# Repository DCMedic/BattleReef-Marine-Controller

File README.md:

# BattleReef Marine Controller

BattleReef Marine Controller is a secure, event-driven cyber-physical platform for marine aquarium monitoring, automation, and device control. The current stack combines a FastAPI/SQLAlchemy backend, TimescaleDB/PostgreSQL telemetry storage, mutually authenticated MQTT transport, an authenticated HTTP control plane, and a React/Vite operator interface.

## Control flow

The normal remote-control lifecycle is intentionally single-path:

1. An authenticated node publishes telemetry over MQTT/TLS.
2. Mosquitto authorizes the certificate identity against the topic ACL.
3. The backend verifies topic/payload identity, evaluates telemetry plausibility, and persists the reading.
4. Implausible readings are retained for forensics as `quality=suspect` but are excluded from trusted automation.
5. Rules, schedules, and the safety watchdog may create a queued command using only recent trusted telemetry where sensor evidence is involved.
6. The command dispatcher publishes the queued command to the target device and marks it `dispatched`.
7. The authenticated device executes the command and publishes an ACK containing its correlation ID and resulting state.
8. The backend verifies device identity, command correlation, and reported state before marking the command completed.
9. Independent physical evidence can then challenge the device's self-reported state.

Publishing a command is not treated as successful actuation. An ACK proves what a device reports; independent physical verification provides a separate evidence layer for what the system appears to be doing physically.

## HTTP authentication and RBAC

The operator API uses Argon2 password hashing and short-lived HS256 bearer tokens. Tokens are bound to username, role, principal type, issuer/audience, and a database token version. Password, role, or activation changes invalidate previously issued sessions. Browser tokens are stored only in `sessionStorage`.

Repeated bad credentials trigger a temporary database-backed lockout. The role hierarchy is `viewer`, `operator`, `engineer`, and `administrator`, with both human `user` and non-interactive `service` principals supported.

## MQTT identity and authorization

MQTT listens on TLS port `8883` and requires an X.509 client certificate. Mosquitto uses certificate CN as MQTT identity, anonymous access is disabled, and broker ACLs restrict nodes/devices to their own telemetry, ACK, and command namespaces.

## Audit trail

Security, command, operator, device-health, telemetry-quarantine, and independent physical-verification transitions are persisted in PostgreSQL as an append-only SHA-256 hash-chained journal. Historical audit events have read/integrity APIs but no update/delete API.

## Telemetry plausibility and quarantine

Before a new reading is trusted, BattleReef evaluates conservative physical bounds and selected rate-of-change/correlation rules. Current examples include temperature, pH, salinity, sump level, dissolved oxygen, ORP, flow, RPM, and dedicated power channels. Large salinity changes are additionally checked against recent sump-level movement from the same authenticated telemetry source.

A failed plausibility check does not delete data. The reading is persisted as `quality=suspect`, a runtime alert is raised, and a durable audit event records the quarantine reason. Automation reads use only `quality=good` telemetry. Temperature automation also rejects trusted readings older than 120 seconds, preventing fallback to stale-but-valid data after a sensor begins producing implausible samples.

The safety watchdog follows the same trust model. Critical temperature/sump actions and threshold evaluation require recent trusted data. Leak probes remain deliberately fail-safe: only a trusted `0.0` reading is accepted as dry.

## Independent physical-state verification

A background verifier runs every 15 seconds and compares fresh device-reported state against fresh independent telemetry.

Return-pump verification can use three separate physical domains: `power_return_pump_main` for electrical consumption, `flow_return_main` for hydraulic delivery, and optional `rpm_return_pump_main` for rotational evidence. A contradiction in any available channel is treated as a critical failure. When only one independent signal is installed and agrees, the verifier reports degraded rather than falsely claiming strong multi-signal verification.

Heater relay state is checked against `power_heater_main`, a dedicated isolated heater-circuit power measurement. Aggregate `power_monitor_main` is intentionally not used for this critical assertion because unrelated loads could create false positives.

Critical sensor values can also be challenged by redundant channels. `tank_temp_verify` is compared with `tank_temp_main`, and `sump_level_verify` is compared with `sump_level_main`. Moderate disagreement produces a degraded warning; disagreement beyond twice the configured tolerance becomes critical.

Independent evidence older than 120 seconds is not used to verify state; the result becomes `unknown`. Critical contradictions raise runtime alerts, create tamper-evident audit events, and impose a large device-health penalty. Degraded verification warnings receive a smaller health penalty. Recovery is audited.

Engineers can manually invoke the verifier at `POST /api/v1/physical-verification/evaluate` in addition to the periodic background evaluation.

## Independent verification hardware package

The hardware contract is versioned under `hardware/`:

- `hardware/verification-package-v1.json` is the machine-readable sensor/evidence manifest and threshold contract.
- `hardware/README.md` describes architecture, isolation requirements, evidence topology, MQTT behavior, and maintenance expectations.
- `hardware/commissioning-checklist-v1.md` is the acceptance checklist for bringing real verification hardware into service.

Version 1 defines dedicated heater and return-pump power channels, return flow, optional pump RPM, a redundant tank-temperature probe, and a redundant sump-level channel. Backend tests verify that every sensor named in the hardware manifest exists in the sensor catalog and that manifest thresholds match runtime verification constants.

Any interface connected to AC mains must be galvanically isolated, enclosed, appropriately listed/certified, and installed according to applicable electrical code and manufacturer instructions. BattleReef GPIO/ADC pins, exposed development boards, breadboards, and water-contact sensors must never be connected directly to mains potential.

## Device health monitoring

BattleReef evaluates device/node health every 30 seconds and persists the latest score in `device_health`. Health uses telemetry/state freshness, telemetry quality, command failures/timeouts, ACK state mismatches, average ACK latency, and active independent physical-verification failures.

Health states are `healthy`, `degraded`, `critical`, and `unknown`. Degraded/critical states create runtime alerts; transitions are written to the audit journal. Authenticated viewers can read `/api/v1/device-health`, while engineers can manually request evaluation at `/api/v1/device-health/evaluate`.

## Development fault injection

`tools/simulator/device_fault_injector.py` exercises the real mTLS command/ACK path with `normal`, `drop_ack`, `delayed_ack`, `wrong_state`, and `explicit_failure` behaviors.

`tools/simulator/physical_fault_injector.py` exercises telemetry plausibility and physical verification using development-only mTLS credentials. Scenarios include salinity spikes, zero/present return flow, return-pump power and RPM contradictions, heater power contradictions, and redundant temperature/sump disagreement.

Examples:

```bash
python tools/simulator/physical_fault_injector.py salinity_spike
python tools/simulator/physical_fault_injector.py return_pump_power_zero
python tools/simulator/physical_fault_injector.py verify_temp_disagreement
python tools/simulator/physical_fault_injector.py heater_power_present
```

The fault injectors are external development tools. No production HTTP endpoint can enable them. Never deploy the aggregate development simulator certificates to production hardware.

## Telemetry contract

Telemetry values are numeric throughout the API/database (`value_double`) and timestamps are normalized to UTC. Leak probes use `0.0 = dry` and `1.0 = wet`. Unknown, suspect, or non-dry leak evidence is treated fail-safe.

Dedicated verification channels must represent independently measured physical evidence rather than copied command values or actuator self-reports.

## Local development

```bash
cp .env.example .env
bash ops/mosquitto/generate-dev-pki.sh
docker compose up --build
```

For backend tests:

```bash
cd backend
python -m venv .venv
# Activate .venv for your platform
python -m pip install --upgrade pip
pip install -e ".[dev]"
MQTT_TLS_ENABLED=false pytest
```

For the frontend:

```bash
cd frontend
cp .env.example .env
npm ci
npm run dev
```

## Production certificate provisioning

Production deployments should use a dedicated BattleReef device CA or enterprise PKI. Each hardware node should receive its own private key/certificate and independently revocable identity.

## Database bootstrap

`ops/postgres/init.sql` owns TimescaleDB-specific telemetry initialization. The backend also runs an idempotent SQLAlchemy schema bootstrap at startup so application schema evolution can occur without destructive database-volume resets.

## Continuous integration

GitHub Actions validates pull requests to `main` with repository hygiene, backend regression tests, frontend build/security audit, Compose validation, and a live MQTT mTLS security integration gate. Plausibility boundaries, fail-safe leak semantics, independent physical verification, and the hardware-manifest/runtime contract are regression tested.

## Safety principles

BattleReef treats automation as a cyber-physical safety system. Safety-critical commands use explicit delivery policies, automation commands are deduplicated, safety/schedule/health/physical-verification loops recover from transient errors, remote commands require authenticated ACKs, independent evidence can contradict device self-reports, implausible telemetry is quarantined rather than trusted, and privileged HTTP actions require an authenticated principal with the appropriate role.

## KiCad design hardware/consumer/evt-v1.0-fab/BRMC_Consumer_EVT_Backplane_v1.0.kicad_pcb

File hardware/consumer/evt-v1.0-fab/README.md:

# BRMC Consumer EVT v1.0 modular backplane

This directory is the controlled engineer-review release for the 220 × 78 mm,
six-layer BRMC Consumer modular prototype backplane. The design is generated
deterministically; review the generated KiCad source and the exact successful
CI manufacturing artifact together.

## Controlled scope

The PCB is a passive module-interconnect backplane. It is not the complete
integrated main logic/power board or rear precision-analog board described by
the older v0.9 architecture. The EVT compute endpoint is an official Raspberry
Pi CM5 IO Board revision 2, independently powered at J11 by an official 27 W
USB-C supply. `J_CM5` is a signal-only 16-circuit interface; CM5 power is not
carried on the backplane.

The current generator implements production geometry for all 13 board
connectors:

- Molex C-Grid III 90130-1216 at `J_CM5` and 90130-1224 at `J_MCU`;
- Molex KK 254 22-23-20x1 headers for sensor, field-bus, safety and service
  interfaces; and
- Molex Micro-Fit 3.0 43045-0600/-0400/-0800 right-angle headers, including
  the manufacturer-pattern locator holes, for `J_PWR`, `J_AO` and `J_PWRMOD`.

`connector-production-verification.csv` freezes the design selection and cites
the governing manufacturer evidence. Independent drawing comparison,
first-article keying/orientation, crimp inspection and mating-access acceptance
remain required approval evidence; the file does not claim those events have
already occurred.

## Electrical definition

The source generator, pinout, interconnect schematic, machine-readable netlist,
power budget and harness schedule together define the board-only electrical
interface. A component-level KiCad schematic/ERC result is not asserted because
this artifact contains no active circuitry. The CI validator instead reconciles
the generated endpoint schedule to the PCB and its IPC-D-356 export.

Power routing uses 1.50 mm `24V_IN` and 2.00 mm `5V_SYS` B.Cu trunks. Connector
fan-out is segregated by copper layer, with L2 and L5 reserved as continuous GND
reference planes. GND connector pads connect directly to those planes. The
review package records calculated interface ceilings, conductor gauges,
maximum harness lengths, warm voltage drop and branch-protection requirements.
Unimplemented PSM-01 and daughtercard circuits must be independently reviewed
as separate design objects and must comply with the controlled ceilings.

## Automated gates

The GitHub workflow regenerates all controlled source and review artifacts,
rejects drift, fills the L2/L5 planes in an archived manufacturing copy, runs
KiCad 9 DRC, exports Gerber/drill/position/IPC-D-356/STEP outputs, reconciles
the netlist, validates the complete package, and checksums every artifact. Only
an artifact from a successful run for the exact reviewed commit is acceptable.

## Review package

Start with `BRMC_Consumer_v1.0_Engineer_Review_Index.md` and
`BRMC_Consumer_v1.0_Electrical_Engineering_Review_Package.pdf`. The
interconnect PDF, CSV schedules, KiCad files, enclosure-base candidate and
external return forms are all included in the CI artifact.

## Release status

`release-status.json` and `release-gate-evidence.json` are authoritative. This
revision is **complete for independent engineering review of the passive
backplane scope**, but it is **not a prototype fabrication release**. The
following approvals/evidence cannot be self-issued and remain external gates:

- responsible mechanical engineer approval of the CNC 6061 base and a
  tolerance-aware populated/harness/thermal/service fit record;
- fabricator-returned stackup and DFM approval tied to the exact CI artifact;
- independent qualified electrical/layout review with all findings closed;
- connector/harness first-article orientation, crimp, continuity and access
  evidence; and
- measured EVT startup, steady-state, transient/fault and thermal evidence.

Commercial production, mains connection, and approval of absent module designs
remain prohibited.

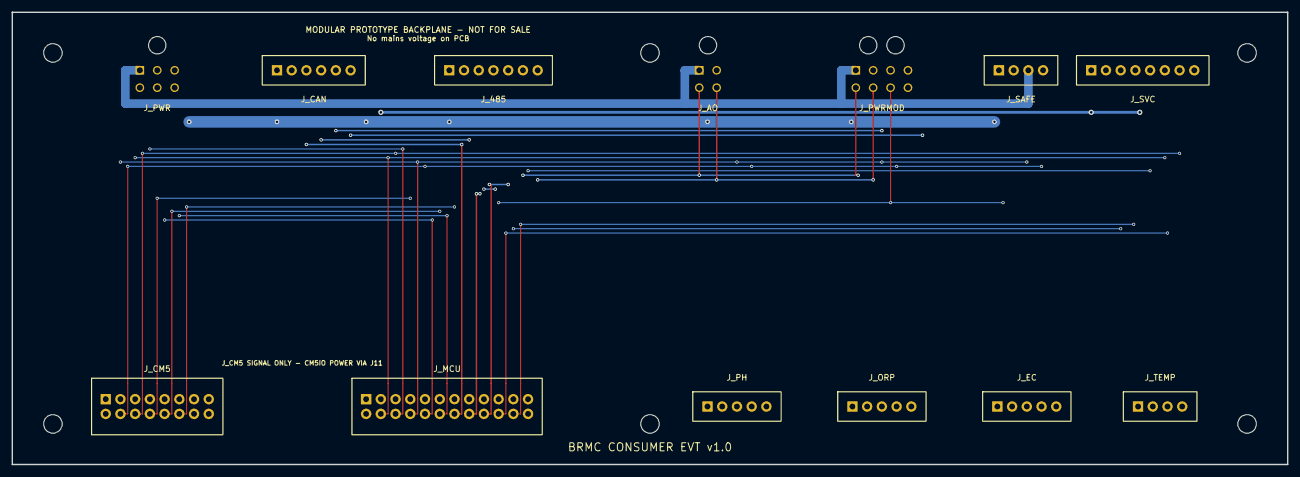
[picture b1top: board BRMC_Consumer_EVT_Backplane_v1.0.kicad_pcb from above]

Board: 6 copper layers, 220.0 x 78.0 mm, 19 parts (0 on the bottom side), 28 nets.

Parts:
H1: MountingHole_3.2mm_M3; MOUNT_M3_H1
H2: MountingHole_3.2mm_M3; MOUNT_M3_H2
H3: MountingHole_3.2mm_M3; MOUNT_M3_H3
H4: MountingHole_3.2mm_M3; MOUNT_M3_H4
H5: MountingHole_3.2mm_M3; MOUNT_M3_H5
H6: MountingHole_3.2mm_M3; MOUNT_M3_H6
J_485: MOLEX_22-23-2071_ISO_RS485_MODULE; HDR_J_485
J_AO: MOLEX_43045-0400_MODBUS_0_10V_8CH; HDR_J_AO
J_CAN: MOLEX_22-23-2061_ISO_CAN_FD_MODULE; HDR_J_CAN
J_CM5: MOLEX_90130-1216_CM5IO_SIGNAL; HDR_J_CM5
J_EC: MOLEX_22-23-2051_ATLAS_EZO_EC_ISO; HDR_J_EC
J_MCU: MOLEX_90130-1224_STM32G0B1_CORE; HDR_J_MCU
J_ORP: MOLEX_22-23-2051_ATLAS_EZO_ORP_ISO; HDR_J_ORP
J_PH: MOLEX_22-23-2051_ATLAS_EZO_PH_ISO; HDR_J_PH
J_PWR: MOLEX_43045-0600_POWER_HARNESS; HDR_J_PWR
J_PWRMOD: MOLEX_43045-0800_POWER_MODULE_BUS; HDR_J_PWRMOD
J_SAFE: MOLEX_22-23-2041_SAFETY_RELAY_DRIVE; HDR_J_SAFE
J_SVC: MOLEX_22-23-2081_SERVICE_DEBUG; HDR_J_SVC
J_TEMP: MOLEX_22-23-2041_DIGITAL_TEMP; HDR_J_TEMP

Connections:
3V3_SYS: J_MCU.3 (3V3_SYS), J_SVC.1 (3V3_SYS), J_TEMP.1 (3V3_SYS)
5V_SYS: J_485.1 (5V_SYS), J_CAN.1 (5V_SYS), J_EC.1 (5V_SYS), J_MCU.1 (5V_SYS), J_ORP.1 (5V_SYS), J_PH.1 (5V_SYS), J_PWR.3 (5V_SYS)
24V_IN: J_AO.1 (24V_IN), J_PWR.1 (24V_IN), J_PWRMOD.1 (24V_IN), J_SAFE.3 (24V_IN)
CAN_H: J_CAN.5 (CAN_H), J_PWRMOD.3 (CAN_H)
CAN_L: J_CAN.6 (CAN_L), J_PWRMOD.4 (CAN_L)
CAN_RX: J_CAN.4 (CAN_RX), J_MCU.15 (CAN_RX)
CAN_TX: J_CAN.3 (CAN_TX), J_MCU.14 (CAN_TX)
CM5_HEARTBEAT: J_CM5.7 (CM5_HEARTBEAT), J_MCU.6 (CM5_HEARTBEAT)
CM5_RX: J_CM5.6 (CM5_RX), J_MCU.5 (CM5_RX), J_SVC.7 (CM5_RX)
CM5_TX: J_CM5.5 (CM5_TX), J_MCU.4 (CM5_TX), J_SVC.6 (CM5_TX)
GND: J_485.2 (GND), J_AO.2 (GND), J_CAN.2 (GND), J_CM5.1 (GND), J_CM5.2 (GND), J_CM5.15 (GND), J_CM5.16 (GND), J_EC.2 (GND), J_MCU.2 (GND), J_MCU.24 (GND), J_ORP.2 (GND), J_PH.2 (GND), J_PWR.2 (GND), J_PWR.4 (GND), J_PWR.6 (GND), J_PWRMOD.2 (GND), J_PWRMOD.8 (GND), J_SAFE.2 (GND), J_SAFE.4 (GND), J_SVC.2 (GND), J_SVC.8 (GND), J_TEMP.2 (GND)
I2C_SCL: J_CM5.3 (I2C_SCL), J_EC.3 (I2C_SCL), J_MCU.8 (I2C_SCL), J_ORP.3 (I2C_SCL), J_PH.3 (I2C_SCL)
I2C_SDA: J_CM5.4 (I2C_SDA), J_EC.4 (I2C_SDA), J_MCU.9 (I2C_SDA), J_ORP.4 (I2C_SDA), J_PH.4 (I2C_SDA)
NRST: J_MCU.23 (NRST), J_SVC.5 (NRST)
RS485_A: J_485.6 (RS485_A), J_AO.3 (RS485_A), J_PWRMOD.5 (RS485_A)
RS485_B: J_485.7 (RS485_B), J_AO.4 (RS485_B), J_PWRMOD.6 (RS485_B)
RS485_DE: J_485.5 (RS485_DE), J_MCU.18 (RS485_DE)
RS485_RX: J_485.4 (RS485_RX), J_MCU.17 (RS485_RX)
RS485_TX: J_485.3 (RS485_TX), J_MCU.16 (RS485_TX)
SAFETY_ACK: J_CM5.8 (SAFETY_ACK), J_MCU.7 (SAFETY_ACK)
SAFETY_ENABLE: J_MCU.19 (SAFETY_ENABLE), J_PWRMOD.7 (SAFETY_ENABLE), J_SAFE.1 (SAFETY_ENABLE)
SPI_CS0: J_CM5.12 (SPI_CS0), J_MCU.13 (SPI_CS0)
SPI_MISO: J_CM5.10 (SPI_MISO), J_MCU.11 (SPI_MISO)
SPI_MOSI: J_CM5.11 (SPI_MOSI), J_MCU.12 (SPI_MOSI)
SPI_SCK: J_CM5.9 (SPI_SCK), J_MCU.10 (SPI_SCK)
SWCLK: J_MCU.22 (SWCLK), J_SVC.4 (SWCLK)
SWDIO: J_MCU.21 (SWDIO), J_SVC.3 (SWDIO)
TEMP_DATA: J_MCU.20 (TEMP_DATA), J_TEMP.3 (TEMP_DATA)

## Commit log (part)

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2026-03-09 new file: .env.example new file: backend/alembic.ini new file: backend/app/api/deps.py new file: backend/app/api/routes/alerts.py new file: backend/app/api/routes/commands.py new file: backend/app/ap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
2026-03-09 new file: .env modified: .env.example new file: backend/app/__pycache__/config.cpython-312.pyc new file: backend/app/__pycache__/main.cpython-312.pyc new file: backend/app/api/routes/__pycache__/heal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
2026-03-10 modified: backend/app/__pycache__/main.cpython-312.pyc modified: backend/app/api/routes/__pycache__/telemetry.cpython-312.pyc modified: backend/app/api/routes/telemetry.py new file: backend/app/db/__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
2026-03-10 modified: backend/app/__pycache__/config.cpython-312.pyc modified: backend/app/__pycache__/main.cpython-312.pyc modified: backend/app/config.py modified: backend/app/main.py new file: backend/app/ser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
2026-03-10 new file: backend/app/mqtt/__pycache__/topics.cpython-312.pyc modified: backend/app/mqtt/topics.py modified: backend/app/services/__pycache__/mqtt_listener.cpython-312.pyc modified: backend/app/servi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
2026-03-10 modified: backend/app/__pycache__/config.cpython-312.pyc modified: backend/app/__pycache__/main.cpython-312.pyc new file: backend/app/api/routes/__pycache__/commands.cpython-312.pyc modified: backend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
2026-03-10 modified: backend/app/services/__pycache__/mqtt_listener.cpython-312.pyc modified: backend/app/services/mqtt_listener.py
2026-03-10 modified: backend/app/__pycache__/main.cpython-312.pyc new file: backend/app/api/routes/__pycache__/device_states.cpython-312.pyc new file: backend/app/api/routes/device_states.py new file: backend/a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
2026-03-10 modified: backend/app/__pycache__/main.cpython-312.pyc modified: backend/app/api/routes/__pycache__/commands.cpython-312.pyc modified: backend/app/main.py modified: backend/app/mqtt/__pycache__/topic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
2026-03-10 modified: backend/app/__pycache__/main.cpython-312.pyc modified: backend/app/mqtt/__pycache__/topics.cpython-312.pyc modified: backend/app/mqtt/topics.py modified: backend/app/services/__pycache__/co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
2026-03-10 modified: backend/app/__pycache__/main.cpython-312.pyc new file: backend/app/api/routes/__pycache__/system.cpython-312.pyc new file: backend/app/api/routes/system.py modified: backend/app/db/models/_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
2026-03-10 modified: frontend/src/api/client.ts modified: frontend/src/api/queries.ts modified: frontend/src/components/DeviceStateTile.tsx modified: frontend/src/components/MetricCard.tsx new file: frontend/sr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
2026-03-10 modified: .env new file: frontend/.env new file: frontend/index.html new file: frontend/node_modules/.bin/baseline-browser-mapping new file: frontend/node_modules/.bin/baseline-browser-mapping.cmd ne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
2026-03-10 Frontend Telemetry Charts
2026-03-11 modified: frontend/src/api/client.ts modified: frontend/src/api/queries.ts new file: frontend/src/components/ManualControlPanel.tsx new file: frontend/src/components/RecentCommandsTable.tsx new file: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
2026-03-11 modified: backend/app/api/routes/__pycache__/device_states.cpython-312.pyc modified: backend/app/api/routes/device_states.py modified: backend/app/services/__pycache__/device_state_service.cpython-31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
2026-03-11 modified: backend/app/services/__pycache__/command_service.cpython-312.pyc modified: backend/app/services/command_service.py modified: frontend/src/components/ManualControlPanel.tsx
2026-03-11 modified: backend/app/api/routes/__pycache__/commands.cpython-312.pyc modified: backend/app/api/routes/commands.py modified: backend/app/services/__pycache__/rule_engine.cpython-312.pyc modified: bac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
2026-03-11 modified: backend/app/__pycache__/main.cpython-312.pyc new file: backend/app/api/routes/__pycache__/schedules.cpython-312.pyc new file: backend/app/api/routes/schedules.py modified: backend/app/db/__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
2026-03-11 modified: frontend/src/api/queries.ts new file: frontend/src/components/ScheduleManagerPanel.tsx modified: frontend/src/pages/Dashboard.tsx modified: frontend/src/types/index.ts
2026-03-11 modified: frontend/src/components/ScheduleManagerPanel.tsx
2026-03-11 modified: frontend/src/api/client.ts modified: frontend/src/api/queries.ts
2026-03-11 new file: frontend/src/components/WeeklyScheduleTimeline.tsx modified: frontend/src/pages/Dashboard.tsx
2026-03-11 Created separate logical pages to fit cards into.
2026-03-11 modified: frontend/src/App.tsx
2026-03-11 modified: frontend/src/App.tsx modified: frontend/src/pages/OperationsPage.tsx
2026-03-16 new file: backend/control/heater_controller.py new file: backend/devices/base_device.py new file: backend/devices/feeder_device.py new file: backend/devices/heater_device.py new file: backend/devices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
2026-03-16 new file: backend/api/devices.py modified: backend/app/api/routes/devices.py modified: backend/app/main.py new file: backend/bootstrap_devices.py modified: backend/control/heater_controller.py modifi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
2026-03-16 modified: backend/app/__pycache__/main.cpython-312.pyc new file: backend/app/api/routes/__pycache__/alerts.cpython-312.pyc new file: backend/app/api/routes/__pycache__/devices.cpython-312.pyc
2026-03-16 modified: backend/app/__pycache__/main.cpython-312.pyc modified: backend/app/api/routes/__pycache__/devices.cpython-312.pyc
2026-03-17 deleted: backend/api/devices.py new file: backend/app/__init__.py new file: backend/app/__pycache__/__init__.cpython-312.pyc new file: backend/app/__pycache__/bootstrap_devices.cpython-312.pyc modifi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
2026-03-17 modified: backend/app/api/routes/__pycache__/commands.cpython-312.pyc modified: backend/app/api/routes/__pycache__/device_states.cpython-312.pyc modified: backend/app/api/routes/__pycache__/health.cp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
2026-03-17 modified: backend/app/__pycache__/main.cpython-312.pyc modified: backend/app/api/routes/__pycache__/alerts.cpython-312.pyc modified: backend/app/api/routes/__pycache__/commands.cpython-312.pyc modifi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
2026-03-17 modified: backend/app/api/routes/commands.py modified: backend/app/main.py modified: backend/app/services/command_dispatcher.py modified: backend/app/services/command_service.py new file: backend/app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
2026-03-18 modified: backend/app/api/routes/alerts.py modified: backend/app/api/routes/health.py new file: backend/app/core/runtime_alerts.py modified: backend/app/main.py new file: backend/app/services/safety_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
2026-03-18 modified: backend/app/__pycache__/main.cpython-312.pyc modified: backend/app/api/routes/__pycache__/alerts.cpython-312.pyc modified: backend/app/api/routes/__pycache__/commands.cpython-312.pyc modifi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
2026-03-18 modified: backend/app/core/__pycache__/api_self_test.cpython-312.pyc modified: backend/app/core/api_self_test.py modified: backend/app/services/__pycache__/command_dispatcher.cpython-312.pyc new file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
2026-03-18 modified: frontend/src/App.tsx modified: frontend/src/pages/DashboardHomePage.tsx
2026-03-24 modified: frontend/src/api/queries.ts new file: frontend/src/hooks/useLiveDeviceState.ts modified: frontend/src/pages/ManualControlPage.tsx new file: frontend/src/types/deviceState.ts
2026-03-24 modified: frontend/src/App.tsx new file: frontend/src/components/GlobalStatusBanner.tsx
2026-03-24 modified: backend/app/api/routes/__pycache__/stream.cpython-312.pyc modified: backend/app/api/routes/stream.py modified: backend/app/services/__pycache__/device_state_service.cpython-312.pyc modified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
2026-03-24 modified: backend/app/api/routes/__pycache__/telemetry.cpython-312.pyc modified: backend/app/api/routes/telemetry.py new file: backend/app/core/__pycache__/sensor_catalog.cpython-312.pyc new file: ba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
2026-03-24 modified: backend/app/services/mqtt_listener.py modified: simulator/publish_simulator.py
2026-03-25 modified: backend/app/__pycache__/main.cpython-312.pyc modified: backend/app/api/routes/__pycache__/stream.cpython-312.pyc modified: backend/app/api/routes/stream.py modified: backend/app/main.py new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
2026-03-25 modified: backend/app/__pycache__/main.cpython-312.pyc modified: backend/app/api/routes/__pycache__/stream.cpython-312.pyc modified: backend/app/api/routes/stream.py modified: backend/app/main.py del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
2026-03-25 modified: backend/app/api/routes/__pycache__/stream.cpython-312.pyc modified: backend/app/api/routes/stream.py new file: backend/app/core/__pycache__/sensor_thresholds.cpython-312.pyc new file: backe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
2026-03-25 modified: backend/app/__pycache__/main.cpython-312.pyc new file: backend/app/api/routes/__pycache__/thresholds.cpython-312.pyc new file: backend/app/api/routes/thresholds.py modified: backend/app/cor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
2026-03-25 modified: backend/app/api/routes/__pycache__/thresholds.cpython-312.pyc modified: backend/app/api/routes/thresholds.py new file: backend/app/core/__pycache__/threshold_presets.cpython-312.pyc new fil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
2026-03-25 modified: simulator/publish_simulator.py
2026-03-25 modified: tools/simulator/publish_telemetry.py
2026-03-25 modified: backend/data/threshold_overrides.json new file: backend/data/threshold_profile.json
2026-03-25 modified: backend/app/api/routes/telemetry.py modified: backend/app/services/__pycache__/telemetry_service.cpython-312.pyc modified: backend/app/services/telemetry_service.py modified: frontend/src/A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
2026-03-26 modified: backend/app/db/models/__pycache__/telemetry.cpython-312.pyc modified: backend/app/db/models/telemetry.py modified: backend/app/services/__pycache__/telemetry_service.cpython-312.pyc modifie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
2026-03-26 modified: backend/app/db/models/__pycache__/telemetry.cpython-312.pyc modified: backend/app/db/models/telemetry.py
2026-03-28 modified: backend/app/db/__pycache__/base.cpython-312.pyc modified: backend/app/db/base.py modified: backend/app/db/models/__pycache__/command.cpython-312.pyc modified: backend/app/db/models/__pycach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
2026-03-28 modified: backend/app/api/routes/__pycache__/telemetry.cpython-312.pyc modified: backend/app/db/__pycache__/session.cpython-312.pyc modified: backend/app/db/base.py new file: backend/app/db/models/__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
